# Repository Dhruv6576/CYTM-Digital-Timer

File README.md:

# CYTM Digital Timer

24 VDC cyclic relay timer: relay ON for a set time, OFF for a set time, repeat.
Nuvoton MG51FB9AE (8051) MCU, 3-digit 7-segment display, SET / START / STOP keys.

| Folder | What |
|--------|------|
| `Final/` | Production firmware `5-26.c` (IAR). `5-26.a51` is an Intel HEX image built from an earlier version of the source; rebuild before flashing. |
| `hardware/` | PCB, generated from scratch with KiCad 10 + Python. See [hardware/README.md](hardware/README.md). |
| `timer_sdcc/` | SDCC display test (cycles 0-9 on all digits). |
| `resources/` | Photos of the previous board, enclosure and a reference film panel. |
| `docs/` | Design spec and build plan for the PCB. |

## Firmware

Settings: hold SET 1 s, choose ON unit (UP = min, DOWN = sec), set ON value, choose OFF unit, set OFF value,
SET saves to flash and restarts the cycle. 30 s without a key cancels. Hold START + STOP 2 s shows the
manufacturing date. Calibrate the clock with `CAL_MS` at the top of `5-26.c`.

Build needs the Nuvoton MG51 BSP headers (`numicro_8051.h`), not included here:
https://github.com/OpenNuvoton/MG51BSP

## PCB

50 x 80 mm, 2 layers. Gerbers, BOM, pick-and-place and 1:1 films are in `hardware/output/`.
Rebuild and re-check everything with `python hardware/scripts/build.py`.

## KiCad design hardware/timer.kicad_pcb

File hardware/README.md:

# CYTM V5 Digital Timer PCB

24 VDC cyclic relay timer board for the firmware in `../Final/5-26.c` (MG51FB9AE, unchanged pin map).
2-layer, 50 x 80 mm, display/LEDs/keys/terminal on the front, everything else on the back.

Status: prototype (Rev A). ERC 0 errors / 0 warnings, DRC 0 violations, 0 unconnected, schematic parity clean.

## Rebuild

Everything is generated from `scripts/circuit.py` (parts, nets, placement). One command rebuilds and checks it all:

```
python scripts/build.py
```

Needs: KiCad 10 (`C:\Program Files\KiCad\10.0`), Python 3.10+ with PyMuPDF, Java 17, and
`tools/freerouting-1.9.0.jar` (not in git; get it with
`gh release download v1.9.0 -R freerouting/freerouting -p freerouting-1.9.0.jar -D hardware/tools`).
`scripts/env.py` holds the paths. Takes about 4 minutes, most of it autorouting and 3D renders.

Freerouting does not give the same tracks on every run. `build.py` only reports `BUILD OK` when the new board
passes every test, ERC and DRC, so any accepted run is clean; the files in `output/` belong to the last run.

| Step | Script | Output |
|------|--------|--------|
| Project libraries | `gen_symlib.py` | `timer.kicad_sym`, `timer.pretty/`, `timer.3dshapes/` |
| Schematic | `gen_sch.py` | `timer.kicad_sch` |
| Board + placement | `gen_pcb.py` (KiCad python) | `timer.kicad_pcb` |
| Routing | `route.py` (KiCad python + Freerouting 1.9.0) | routed `timer.kicad_pcb` |
| Fabrication files | `export.py` | `output/` |
| Films | `films.py` | `output/films_panel_3x2.pdf` |
| Checks | `tests/*.py`, ERC, DRC | `output/erc.rpt`, `output/drc.rpt` |

## Outputs (`output/`)

- `gerbers.zip`: Gerber X2 (both copper, mask, paste, legend, outline) + Excellon drill. Upload to the PCB maker.
- `bom.csv`: parts grouped by value and footprint.
- `positions.csv`: pick-and-place, mm, origin at the board's bottom-left corner.
- `schematic.pdf`
- `render_top.png`, `render_bottom.png`, `render_iso.png`
- `films_panel_3x2.pdf`: 1:1 films, 3 x 2 panel, one page per layer (back layers mirrored, mask negative).
  Check the 10 mm scale bar after printing.

## Circuit summary

- 24 V in: SMBJ28CA bidirectional TVS on the raw input, then SS36 (60 V) reverse-polarity diode,
  100 uF bulk, L78M05 (DPAK) to 5 V.
- Relay: SRD-24VDC-SL-C, 24 V coil from the protected rail, MMBTA06 driver (80 V), 1N4148W flyback.
  COM is fed from raw IN+ so load current bypasses the diode. IN+ -> COM, NO -> OUT+ and IN- <-> OUT- are 3 mm tracks (5 A).
- Display: 3-digit 0.56" common anode (BA56-12EWA pinout). Each digit and the LED group is driven by an
  SS8050 emitter follower, so "pin high = digit on" (firmware polarity) and the digit pins carry only base
  current. The 8 segment pins each sink their segment current through 330 ohm (~4.5-6 mA peak).
- The 3 mm load tracks are not tinned (no mask opening): they run under the terminal and relay bodies.
  3 mm of 1 oz copper carries 5 A at about 10 C rise.
- LEDs on the LED group (P0.6): SEC = seg A, ON/OFF = seg B (relay on), MIN = seg C, SET = seg F (setting mode).
- Keys to GND: SET P1.7, START P2.0 (10k pull-up), STOP P3.0.
- ICP header J2: 1 VDD, 2 ICE_DAT (P1.6), 3 ICE_CLK (P0.2), 4 nRST (P2.0), 5 GND.

## Before ordering in volume

1. **MCU pinout.** The MG51FB9AE symbol assumes the N76E003 / MS51FB9AE TSSOP-20 pinout
   (`scripts/gen_symlib.py`, checked by `tests/test_libs.py`). Confirm it against the Nuvoton MG51 datasheet.
2. **Display.** Pinout taken from Kingbright CA56-12 with pin 6 not connected (3-digit BA56-12EWA, 37.8 x 19 mm).
   Confirm the part you buy uses the same 12-pin layout.
3. **Enclosure.** Board size, display, key, LED, hole and terminal positions are assumptions. Measure the
   enclosure and change the coordinates in `scripts/circuit.py`, then run `build.py`.
4. **Firmware.** The SEC and MIN LEDs are wired (seg A / seg C in the LED-group slot) but the current firmware
   does not light them. ON/OFF and SET already work.
5. **Relay rating.** The tracks carry 5 A. The SRD relay is rated 10 A, but the terminal block and board are not.
6. **Surges.** The L78M05 is rated 35 V; the SMBJ28CA clamps up to 45 V on a full-energy surge. For harsh
   supplies use a 40 V+ regulator (or a small buck converter) in the same position.
7. **Prototype checks.** Measure the regulator tab temperature (about 0.9 W at 24 V) and the display brightness
   (330 ohm gives about 1.2-1.5 mA average per segment; 220 ohm is brighter but heats the regulator more).
8. **Inductive loads.** For valves or contactor coils on OUT, fit a freewheel diode at the load.

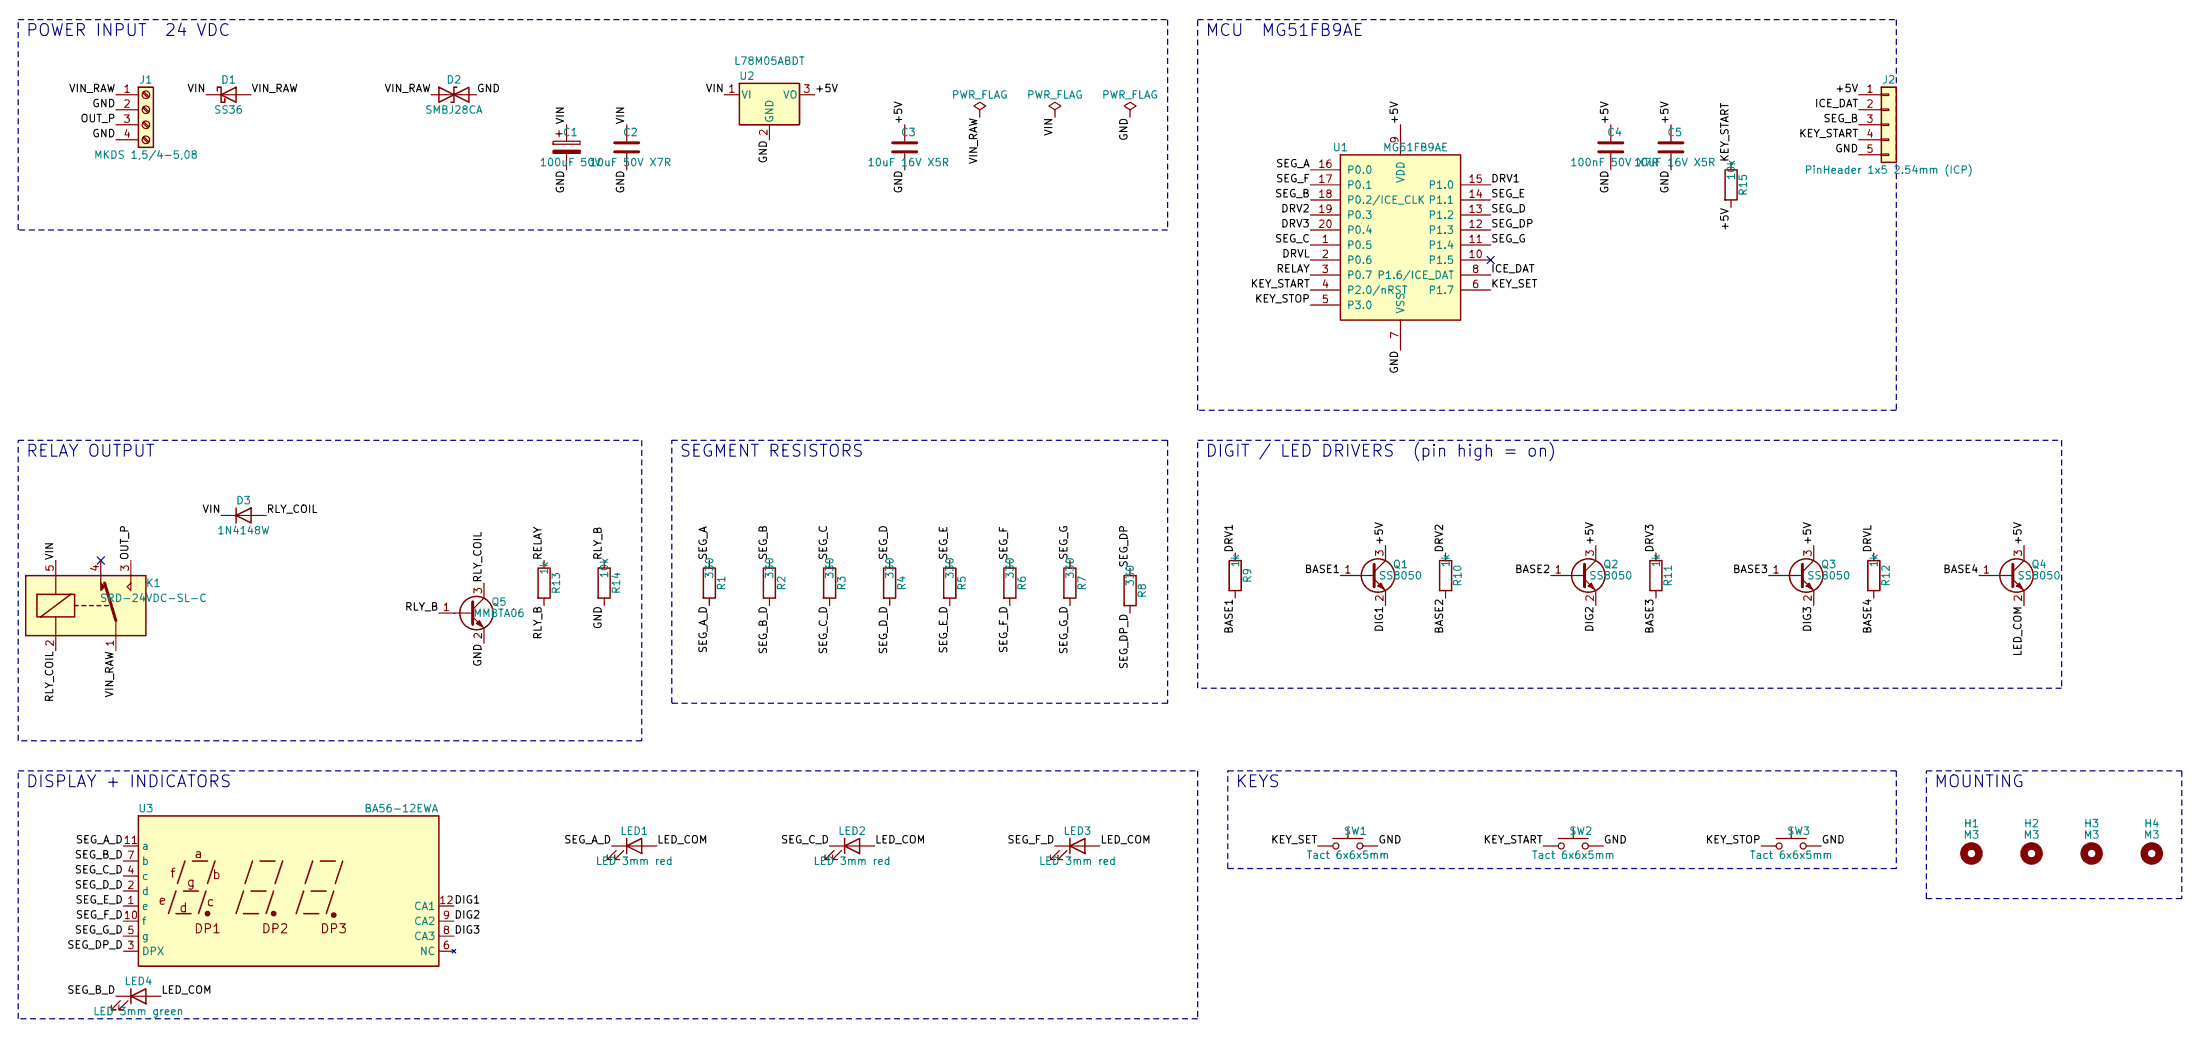
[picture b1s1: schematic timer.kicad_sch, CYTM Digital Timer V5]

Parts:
C1: 100uF 50V; CP_Radial_D8.0mm_P3.50mm
C2: 10uF 50V X7R; C_1206_3216Metric
C3, C5: 10uF 16V X5R; C_0805_2012Metric
C4: 100nF 50V X7R; C_0805_2012Metric
D1: SS36; D_SMA
D2: SMBJ28CA; D_SMB
D3: 1N4148W; D_SOD-123
H1, H2, H3, H4: M3; MountingHole_3.2mm_M3
J1: MKDS 1,5/4-5,08; TerminalBlock_Phoenix_MKDS-1,5-4-5.08_1x04_P5.08mm_Horizont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
J2: PinHeader 1x5 2.54mm (ICP); PinHeader_1x05_P2.54mm_Vertical
K1: SRD-24VDC-SL-C; Relay_SPDT_SANYOU_SRD_Series_Form_C
LED1, LED2, LED3: LED 3mm red; LED_D3.0mm
LED4: LED 3mm green; LED_D3.0mm
Q1, Q2, Q3, Q4: SS8050; SOT-23
Q5: MMBTA06; SOT-23
R1, R2, R3, R4, R5, R6, R7, R8: 330; R_0805_2012Metric
R9, R10, R11, R12, R13: 1k; R_0805_2012Metric
R14, R15: 10k; R_0805_2012Metric
SW1, SW2, SW3: Tact 6x6x5mm; SW_PUSH_6mm
U1: MG51FB9AE; TSSOP-20_4.4x6.5mm_P0.65mm
U2: L78M05ABDT; TO-252-2
U3: BA56-12EWA; Display_3Digit_0.56in_CA

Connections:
/+5V: C3.1, C4.1, C5.1, J2.1, Q1.3 (C), Q2.3 (C), Q3.3 (C), Q4.3 (C), R15.2, U1.9 (VDD), U2.3 (VO)
/BASE1: Q1.1 (B), R9.2
/BASE2: Q2.1 (B), R10.2
/BASE3: Q3.1 (B), R11.2
/BASE4: Q4.1 (B), R12.2
/DIG1: Q1.2 (E), U3.12 (CA1)
/DIG2: Q2.2 (E), U3.9 (CA2)
/DIG3: Q3.2 (E), U3.8 (CA3)
/DRV1: R9.1, U1.15 (P1.0)
/DRV2: R10.1, U1.19 (P0.3)
/DRV3: R11.1, U1.20 (P0.4)
/DRVL: R12.1, U1.2 (P0.6)
/GND: C1.2, C2.2, C3.2, C4.2, C5.2, D2.2 (A2), J1.2, J1.4, J2.5, Q5.2 (E), R14.2, SW1.2, SW2.2, SW3.2, U1.7 (VSS), U2.2 (GND)
/ICE_DAT: J2.2, U1.8 (P1.6/ICE_DAT)
/KEY_SET: SW1.1, U1.6 (P1.7)
/KEY_START: J2.4, R15.1, SW2.1, U1.4 (P2.0/nRST)
/KEY_STOP: SW3.1, U1.5 (P3.0)
/LED_COM: LED1.2 (A), LED2.2 (A), LED3.2 (A), LED4.2 (A), Q4.2 (E)
/OUT_P: J1.3, K1.3
/RELAY: R13.1, U1.3 (P0.7)
/RLY_B: Q5.1 (B), R13.2, R14.1
/RLY_COIL: D3.2 (A), K1.2, Q5.3 (C)
/SEG_A: R1.1, U1.16 (P0.0)
/SEG_A_D: LED1.1 (K), R1.2, U3.11 (a)
/SEG_B: J2.3, R2.1, U1.18 (P0.2/ICE_CLK)
/SEG_B_D: LED4.1 (K), R2.2, U3.7 (b)
/SEG_C: R3.1, U1.1 (P0.5)
/SEG_C_D: LED2.1 (K), R3.2, U3.4 (c)
/SEG_D: R4.1, U1.13 (P1.2)
/SEG_DP: R8.1, U1.12 (P1.3)
/SEG_DP_D: R8.2, U3.3 (DPX)
/SEG_D_D: R4.2, U3.2 (d)
/SEG_E: R5.1, U1.14 (P1.1)
/SEG_E_D: R5.2, U3.1 (e)
/SEG_F: R6.1, U1.17 (P0.1)
/SEG_F_D: LED3.1 (K), R6.2, U3.10 (f)
/SEG_G: R7.1, U1.11 (P1.4)
/SEG_G_D: R7.2, U3.5 (g)
/VIN: C1.1, C2.1, D1.1 (K), D3.1 (K), K1.5, U2.1 (VI)
/VIN_RAW: D1.2 (A), D2.1 (A1), J1.1, K1.1

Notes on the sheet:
POWER INPUT 24 VDC
MCU MG51FB9AE
RELAY OUTPUT
SEGMENT RESISTORS
DIGIT / LED DRIVERS (pin high = on)
DISPLAY + INDICATORS
KEYS
MOUNTING

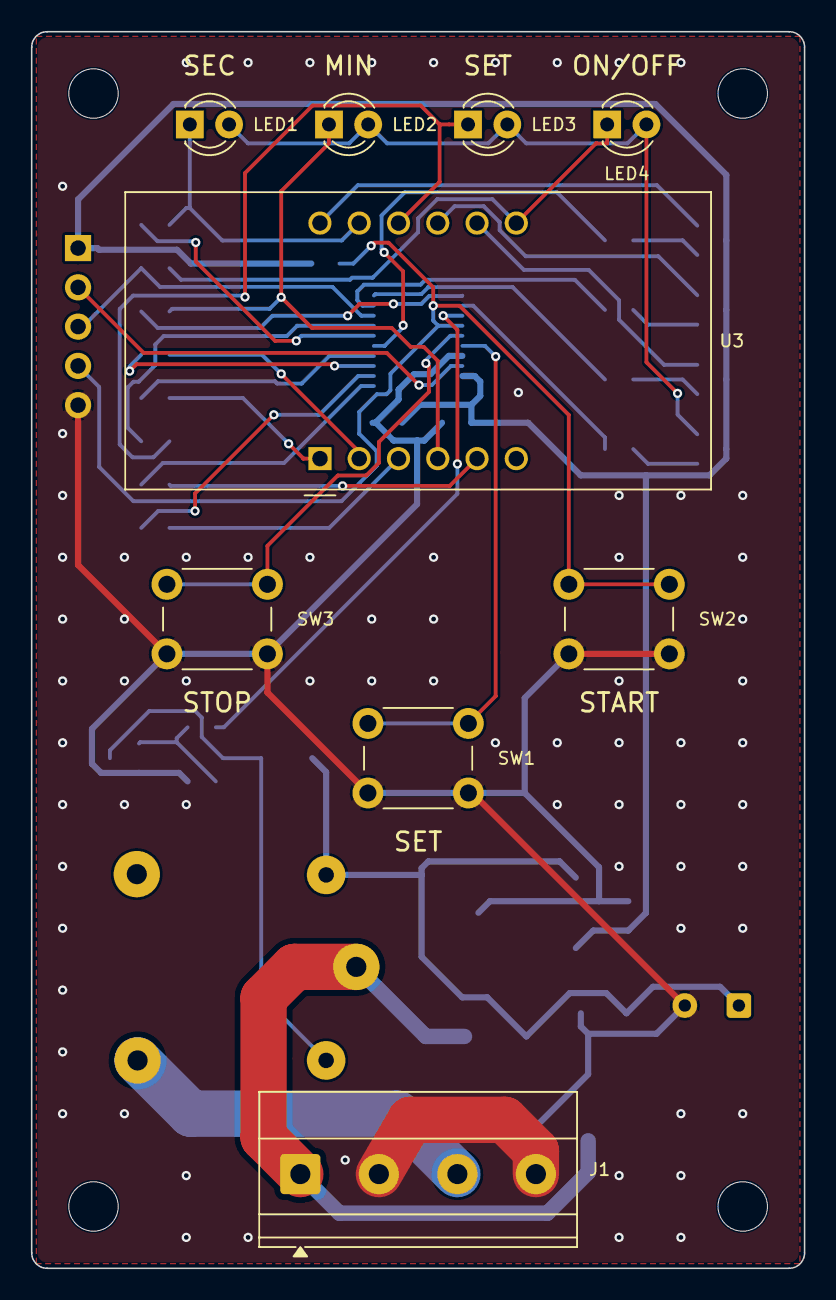
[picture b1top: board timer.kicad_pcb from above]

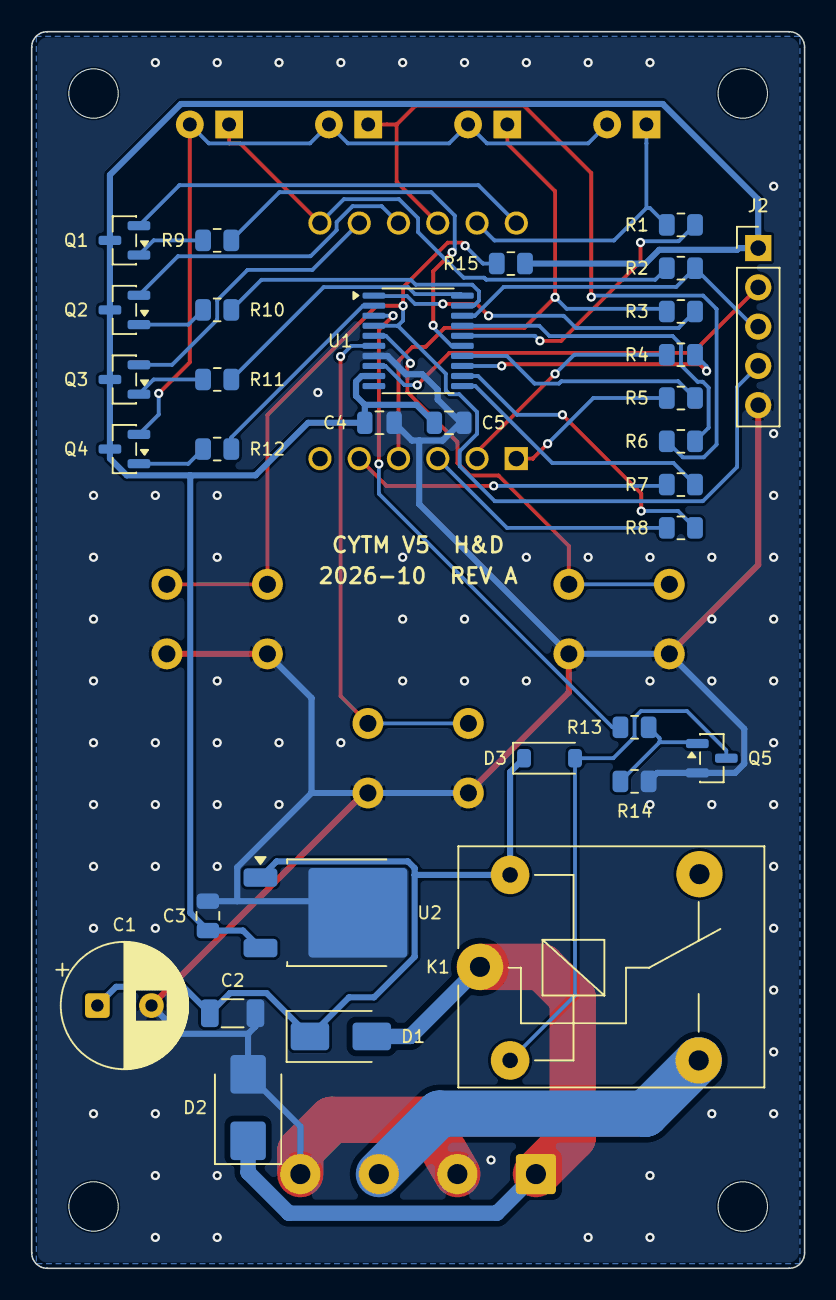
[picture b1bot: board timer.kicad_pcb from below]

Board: 2 copper layers, 50.0 x 80.0 mm, 45 parts (32 on the bottom side), 40 nets.

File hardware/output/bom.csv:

"Refs","Value","Footprint","Qty"
"C1","100uF 50V","Capacitor_THT:CP_Radial_D8.0mm_P3.50mm","1"
"C2","10uF 50V X7R","Capacitor_SMD:C_1206_3216Metric","1"
"C3,C5","10uF 16V X5R","Capacitor_SMD:C_0805_2012Metric","2"
"C4","100nF 50V X7R","Capacitor_SMD:C_0805_2012Metric","1"
"D1","SS36","Diode_SMD:D_SMA","1"
"D2","SMBJ28CA","Diode_SMD:D_SMB","1"
"D3","1N4148W","Diode_SMD:D_SOD-123","1"
"J1","MKDS 1,5/4-5,08","TerminalBlock_Phoenix:TerminalBlock_Phoenix_MKDS-1,5-4-5.08_1x04_P5.08mm_Horizontal","1"
"J2","PinHeader 1x5 2.54mm (ICP)","Connector_PinHeader_2.54mm:PinHeader_1x05_P2.54mm_Vertical","1"
"K1","SRD-24VDC-SL-C","Relay_THT:Relay_SPDT_SANYOU_SRD_Series_Form_C","1"
"LED1,LED2,LED3","LED 3mm red","LED_THT:LED_D3.0mm","3"
"LED4","LED 3mm green","LED_THT:LED_D3.0mm","1"
"Q1,Q2,Q3,Q4","SS8050","Package_TO_SOT_SMD:SOT-23","4"
"Q5","MMBTA06","Package_TO_SOT_SMD:SOT-23","1"
"R1,R2,R3,R4,R5,R6,R7,R8","330","Resistor_SMD:R_0805_2012Metric","8"
"R9,R10,R11,R12,R13","1k","Resistor_SMD:R_0805_2012Metric","5"
"R14,R15","10k","Resistor_SMD:R_0805_2012Metric","2"
"SW1,SW2,SW3","Tact 6x6x5mm","Button_Switch_THT:SW_PUSH_6mm","3"
"U1","MG51FB9AE","Package_SO:TSSOP-20_4.4x6.5mm_P0.65mm","1"
"U2","L78M05ABDT","Package_TO_SOT_SMD:TO-252-2","1"
"U3","BA56-12EWA","timer:Display_3Digit_0.56in_CA","1"
